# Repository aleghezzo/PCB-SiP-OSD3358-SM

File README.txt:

# 4 Layer PCB Based on SiP OSD3358-SM.
## Power Source - SMPS de 12/24V a 5V.
## LDO 3.3V.
## 2 USB Connectors: Host A y Device Micro B.
## MicroSD

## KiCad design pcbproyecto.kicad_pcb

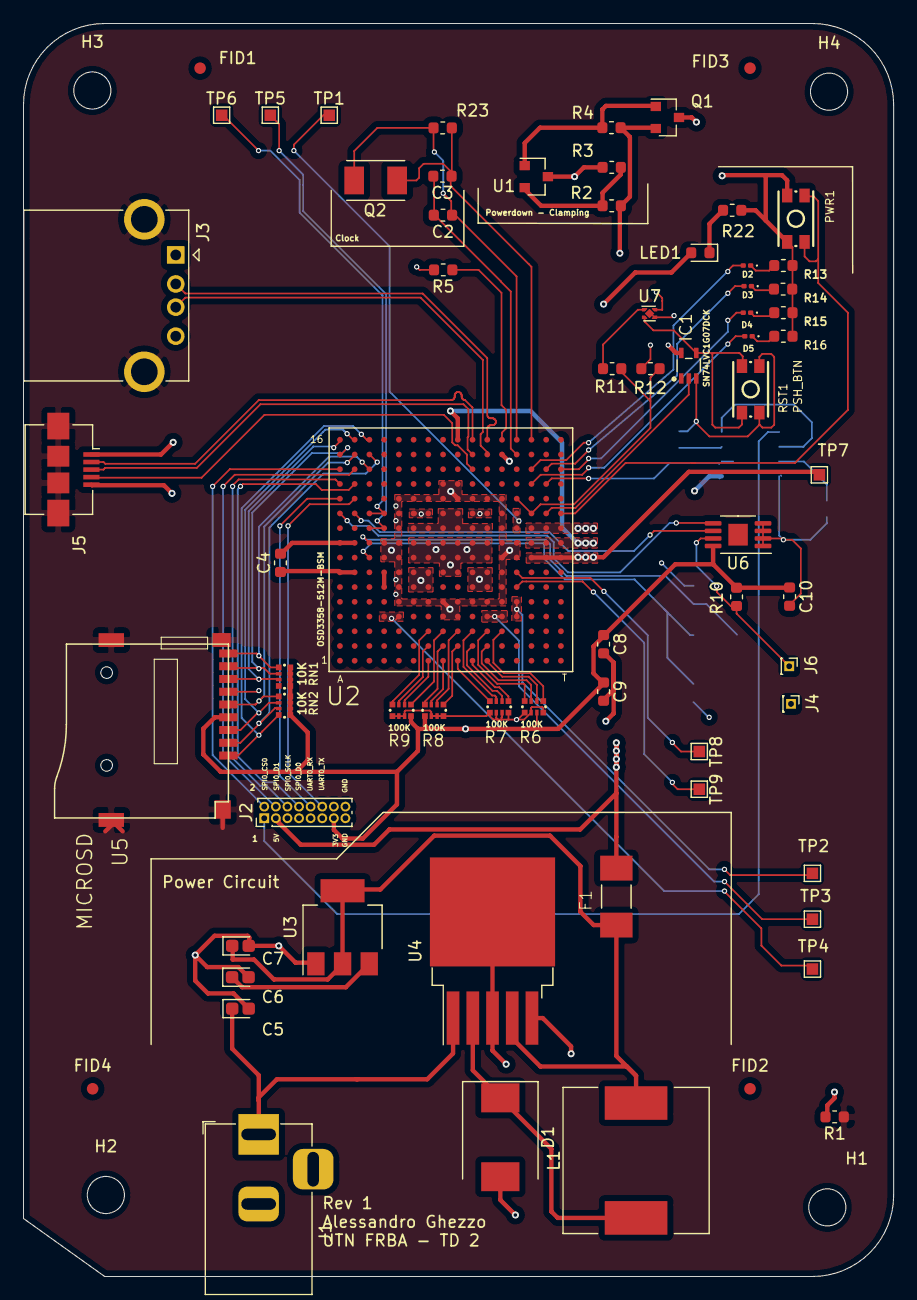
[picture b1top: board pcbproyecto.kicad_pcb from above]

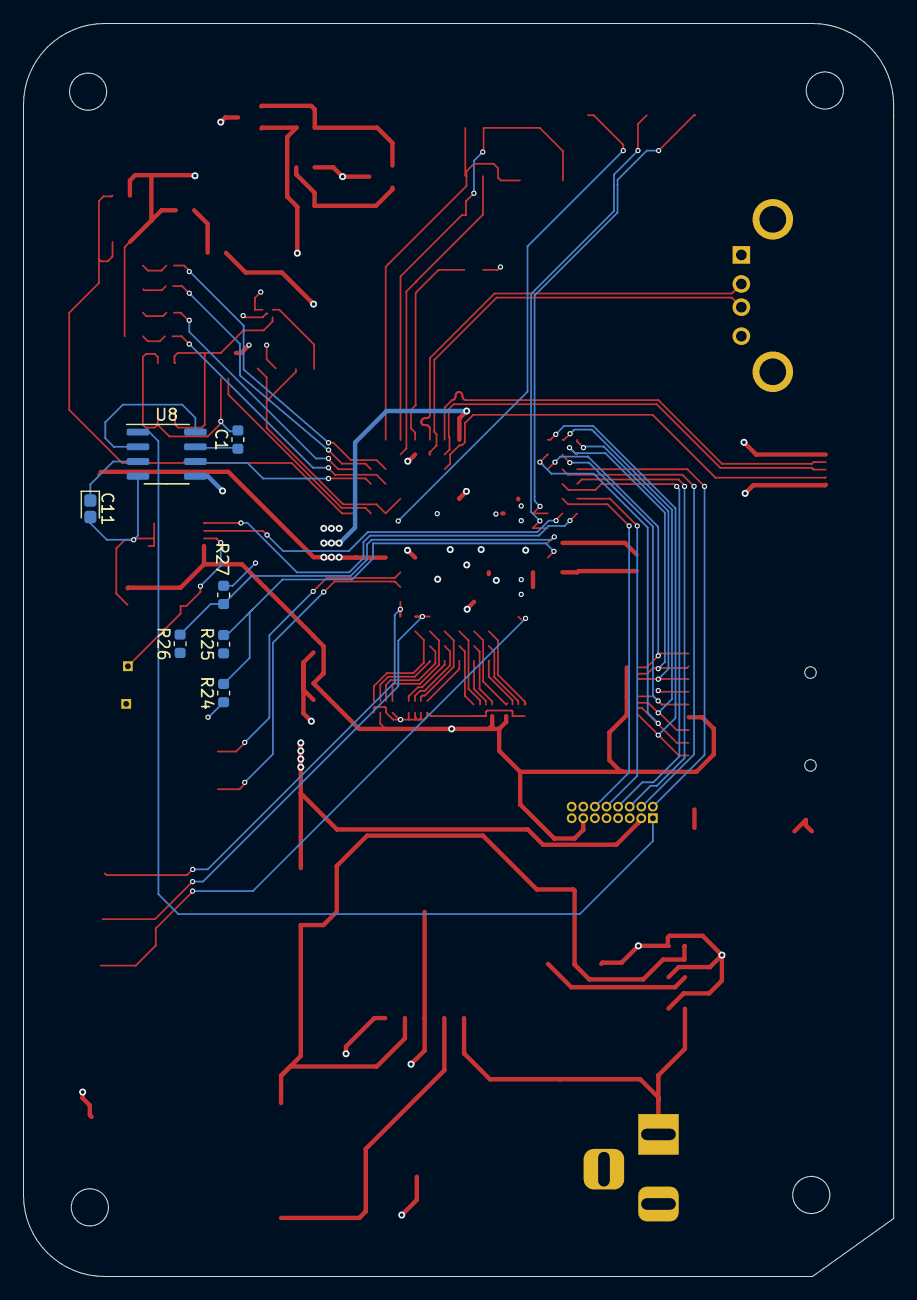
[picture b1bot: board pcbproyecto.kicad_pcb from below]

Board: 4 copper layers, 75.0 x 108.0 mm, 79 parts (7 on the bottom side), 91 nets.

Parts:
C1: 22pF; C_0603_1608Metric
C2, C3: 18pF, 50V; C_0603_1608Metric
C4, C10: 0.1uF, 6.3V; C_0603_1608Metric
C5: 100uF; CP_EIA-1608-08_AVX-J
C6: 100u; CP_EIA-1608-08_AVX-J
C7: 1000u; CP_EIA-1608-08_AVX-J
C8: 10uF, 10V; C_0603_1608Metric
C9: 0.1uF 6,3V; C_0603_1608Metric
C11: 470nF; CP_EIA-1608-08_AVX-J
D1: D_Schottky; D_SMC
D2, D3, D4, D5: LED; LED_0201_0603Metric
F1: Fuse; FUSC6125X279N
FID1, FID2, FID3, FID4: Fiducial; Fiducial_1mm_Mask2mm
H1, H2, H3, H4: MGT; MountingHole_3.2mm_M3
IC1: SN74LVC1G07DCK; SC70(TI-DCK)
J1: Barrel_Jack_Switch; BarrelJack_Horizontal
J2: Peripheral Header; PinHeader_2x08_P1.00mm_Vertical
J3: USB_A; USB_A_CONNFLY_DS1095-WNR0
J4: EEPROM_GND; PinHeader_1x01_P1.00mm_Vertical
J5: USB_B_Micro; USB_Micro-B_Amphenol_10104110_Horizontal
J6: EEPROM_WP; PinHeader_1x01_P1.00mm_Vertical
L1: 100uH; L_12x12mm_H6mm
LED1: L_PWR; LED_0603_1608Metric
PWR1: PSH_BTN; MINI_PUSHBUTTON
Q1: MMBT3906; SOT-23
Q2: 24 MHz; Crystal_SMD_TXC_7A-2Pin_5x3.2mm
R1: 0.1 5%; R_0603_1608Metric
R2, R5, R10, R24, R25, R26, R27: 10K; R_0603_1608Metric
R3: 40K; R_0603_1608Metric
R4: 500; R_0603_1608Metric
R6, R7, R8, R9: 100K; RN0804
R11, R12: 100K; R_0603_1608Metric
R13, R14, R15, R16: 1.5K; R_0603_1608Metric
R22: 1K; R_0603_1608Metric
R23: 1M , 1%; R_0603_1608Metric
RN1, RN2: 10K; RN0804
RST1: PSH_BTN; MINI_PUSHBUTTON
TP1: TP_PWR_EN; TestPoint_Pad_1.0x1.0mm
TP2: TP_PWRONSTN; TestPoint_Pad_1.0x1.0mm
TP3: TP_WAKEUP; TestPoint_Pad_1.0x1.0mm
TP4: TP_EXTINTN; TestPoint_Pad_1.0x1.0mm
TP5: TP_I2C_SCL; TestPoint_Pad_1.0x1.0mm
TP6: TP_I2C_SDA; TestPoint_Pad_1.0x1.0mm
TP7: TP_VIN_BAT; TestPoint_Pad_1.0x1.0mm
TP8: TP_SENSE_BAT; TestPoint_Pad_1.0x1.0mm
TP9: TP_TS_BAT; TestPoint_Pad_1.0x1.0mm
U1: TLVH431; SOT-23
U2: OSD3358-512M-BSM; OSD335X-BGA-256
U3: LM117_TO3; SOT-223-3_TabPin2
U4: LM2576HVS-5; TO-263-5_TabPin3
U5: MICROSD
U6: 24LC32; MSOP-8-1EP_3x3mm_P0.65mm_EP1.68x1.88mm
U7: TPS3831; Texas_X2SON-4_1x1mm_P0.65mm
U8: PCF8883; SOIC-8_3.9x4.9mm_P1.27mm

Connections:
+3V3: C6.1, U3.3
+5V: C7.1, F1.1, L1.2, U3.2, U4.4
/GPIO_A4: U2.R13, U8.6
/GPIO_A5: D5.2, U2.P13
/GPIO_A6: D4.2, U2.T14
/GPIO_A7: D3.2, U2.R14
/GPIO_A8: D2.2, U2.P14
/I2C1_SCL: U2.B11, U6.6
/I2C1_SDA: U2.A11, U6.5
/Interfaces/IN_PWR_SUPPLY: C5.1, J1.1, U4.1
/Interfaces/MMC0_CD: RN2.5, U2.C14, U5.9
/Interfaces/MMC0_CLK: RN1.5, U2.B15, U5.5
/Interfaces/MMC0_CMD: RN1.6, U2.B16, U5.3
/Interfaces/MMC0_DAT0: RN2.7, U2.A16, U5.7
/Interfaces/MMC0_DAT1: RN2.6, U2.A15, U5.8
/Interfaces/MMC0_DAT2: RN1.8, U2.C16, U5.1
/Interfaces/MMC0_DAT3: RN1.7, U2.C15, U5.2
/Interfaces/PWR_ON: PWR1.3, PWR1.4, U2.T11
/PMIC_PGOOD: IC1.2, U2.R11
/Peripherals/SPI0_CS0: J2.2, U2.A14
/Peripherals/SPI0_D0: J2.8, U2.B13
/Peripherals/SPI0_D1: J2.4, U2.B14
/Peripherals/SPI0_SCLK: J2.6, U2.A13
/Peripherals/UART0_RX: J2.10, U2.A12
/Peripherals/UART0_TX: J2.12, U2.B12
/Sistem In Package/AIN51.8V: R24.2, R25.2, U2.C8
/Sistem In Package/AIN61.8V: R26.2, R27.2, U2.C9
/Sistem In Package/LCD_D0_G3: R9.8, U2.G3
/Sistem In Package/LCD_D1_G2: R9.7, U2.G2
/Sistem In Package/LCD_D2_G1: R9.6, U2.G1
/Sistem In Package/LCD_D3_H3: R9.5, U2.H3
/Sistem In Package/LCD_D4_H2: R8.8, U2.H2
/Sistem In Package/LCD_D5_H1: R8.7, U2.H1
/Sistem In Package/LCD_D6_J3: R8.6, U2.J3
/Sistem In Package/LCD_D7_J2: R8.5, U2.J2
/Sistem In Package/LCD_D8_J1: R7.8, U2.J1
/Sistem In Package/LCD_D9_K3: R7.7, U2.K3
/Sistem In Package/LCD_D10_K2: R7.6, U2.K2
/Sistem In Package/LCD_D11_K1: R7.5, U2.K1
/Sistem In Package/LCD_D12_L3: R6.8, U2.L3
/Sistem In Package/LCD_D13_L2: R6.7, U2.L2
/Sistem In Package/LCD_D14_L1: R6.6, U2.L1
/Sistem In Package/LCD_D15_M3: R6.5, U2.M3
/Sistem In Package/OSC_GND: C2.2, C3.2, U2.N15
/Sistem In Package/OSC_IN: C3.1, Q2.2, R23.1, U2.P16
/Sistem In Package/OSC_OUT: C2.1, Q2.1, R23.2, U2.N16
/Sistem In Package/VREF+: C4.1, U2.A7, U2.B7
/Sistem In Package/VREF-: C4.2, U2.A9, U2.B9
/USB0_D+: J5.3, U2.K15
/USB0_D-: J5.2, U2.K16
/USB0_ID: J5.4, U2.K14
/USB1_D+: J3.3, U2.L15
/USB1_D-: J3.2, U2.L16
/USB1_VBU: J3.1, U2.M15
/WARMRST: R11.1, R12.1, U2.N12, U2.P11
CGND: J3.5, J5.6, R1.1, U5.G1, U5.G2, U5.G3, U5.G4
GND: C1.2, C5.2, C6.2, C7.2, C8.2, C9.2, C10.2, C11.2, D1.2, IC1.3, J1.2, J1.3, J2.15, J2.16, J3.4, J4.1, J5.5, PWR1.1, PWR1.2, R1.2, R5.2, R6.1, R6.2, R6.4, R7.1, R7.2, R7.3, R7.4, R8.2, R8.3, R8.4, R9.1, R9.2, R9.3, R12.2, R13.2, R14.2, R15.2, R16.2, R22.2, R24.1, R27.1, RST1.1, RST1.2, U2.D8, U2.D9, U2.E5, U2.E6, U2.E7, U2.E8, U2.E9, U2.E10, U2.E11, U2.E12, U2.F5, U2.F12, U2.G5, U2.G12, U2.H4, U2.H5, U2.H12, U2.H13, U2.J4, U2.J5, U2.J12, U2.J13, U2.K5, U2.K12, U2.L5, U2.L12, U2.M5, U2.M6, U2.M7, U2.M8, U2.M9, U2.M10, U2.M11, U2.M12, U2.N8, U2.N9, U3.1, U4.3, U4.5, U5.6, U6.1, U6.2, U6.3, U6.4, U7.3, U7.5, U8.4
unnamed: C1.1, U8.7
unnamed: C11.1, U8.3
unnamed: D1.1, L1.1, U4.2
unnamed: D2.1, R13.1
unnamed: D3.1, R14.1
unnamed: D4.1, R15.1
unnamed: D5.1, R16.1
unnamed: IC1.4, RST1.3, RST1.4, U7.2
unnamed: J2.1, U8.1
unnamed: J6.1, R10.2, U6.7
unnamed: LED1.1, R22.1
unnamed: Q1.1, R4.1, U1.1
unnamed: R2.2, R3.2, U1.2
unnamed: R5.1, U2.M16
unnamed: R11.2, U7.1
unnamed: TP1.1, U2.N10, U2.N11
unnamed: TP2.1, U2.N4, U2.N5
unnamed: TP3.1, U2.L4, U2.M4
unnamed: TP4.1, U2.D4, U2.E4
unnamed: TP5.1, U2.C10, U2.D10
unnamed: TP6.1, U2.C11, U2.D11
unnamed: TP7.1, U2.P8, U2.R8, U2.T8
unnamed: TP8.1, U2.N7
unnamed: TP9.1, U2.N6
unnamed: U2.D6, U2.D7
unnamed: U8.2, U8.8
SYS_5V: U2.K6, U2.K7, U2.L6, U2.L7
USB_DC: J5.1, U2.J16, U2.P9, U2.R9, U2.T9
VDD_1V8: U2.F10, U2.G10, U2.H10, U2.H11, U2.J10, U2.J11, U2.K10, U2.L10
VDD_3V3A: U2.F8, U2.F9, U2.G8, U2.G9, U2.H7, U2.H8, U2.H9, U2.J7, U2.J8, U2.J9, U2.K8, U2.K9, U2.L8, U2.L9
VDD_3V3AUX: LED1.2, U2.F11, U2.G11
VDD_3V3B: C8.1, C9.1, C10.1, J2.13, Q1.2, R2.1, R4.2, R6.3, R8.1, R9.4, R10.1, RN1.1, RN1.2, RN1.3, RN1.4, RN2.1, RN2.2, RN2.3, RN2.4, U2.F6, U2.F7, U2.G6, U2.G7, U5.4, U6.8, U7.4, U8.5
VDD_5V: F1.2, J2.3, U2.P10, U2.R10, U2.T10
VDD_RTC: IC1.5, Q1.3, R3.1, U1.3, U2.K11, U2.L11

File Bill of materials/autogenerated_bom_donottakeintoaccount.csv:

"Id";"Designator";"Package";"Quantity";"Designation";"Supplier and ref";
1;"F1";"FUSC6125X279N";1;"Fuse";;;
2;"C10,C4";"C_0603_1608Metric";2;"0.1uF, 6.3V";;;
3;"C9";"C_0603_1608Metric";1;"0.1uF 6,3V";;;
4;"C8";"C_0603_1608Metric";1;"10uF, 10V";;;
5;"C3,C2";"C_0603_1608Metric";2;"18pF, 50V";;;
6;"C1";"C_0603_1608Metric";1;"22pF";;;
7;"J3";"USB_A_CONNFLY_DS1095-WNR0";1;"USB_A";;;
8;"U8";"SOIC-8_3.9x4.9mm_P1.27mm";1;"PCF8883";;;
9;"C11";"CP_EIA-1608-08_AVX-J";1;"470nF";;;
10;"TP9";"TestPoint_Pad_1.0x1.0mm";1;"TP_TS_BAT";;;
11;"TP8";"TestPoint_Pad_1.0x1.0mm";1;"TP_SENSE_BAT";;;
12;"RST1,PWR1";"MINI_PUSHBUTTON";2;"PSH_BTN";;;
13;"R16,R15,R14,R13";"R_0603_1608Metric";4;"1.5K";;;
14;"D5,D4,D3,D2";"LED_0201_0603Metric";4;"LED";;;
15;"U7";"Texas_X2SON-4_1x1mm_P0.65mm";1;"TPS3831";;;
16;"R12,R11";"R_0603_1608Metric";2;"100K";;;
17;"IC1";"SC70(TI-DCK)";1;"SN74LVC1G07DCK";;;
18;"U6";"MSOP-8-1EP_3x3mm_P0.65mm_EP1.68x1.88mm";1;"24LC32";;;
19;"TP7";"TestPoint_Pad_1.0x1.0mm";1;"TP_VIN_BAT";;;
20;"TP6";"TestPoint_Pad_1.0x1.0mm";1;"TP_I2C_SDA";;;
21;"TP5";"TestPoint_Pad_1.0x1.0mm";1;"TP_I2C_SCL";;;
22;"TP4";"TestPoint_Pad_1.0x1.0mm";1;"TP_EXTINTN";;;
23;"TP3";"TestPoint_Pad_1.0x1.0mm";1;"TP_WAKEUP";;;
24;"TP2";"TestPoint_Pad_1.0x1.0mm";1;"TP_PWRONSTN";;;
25;"TP1";"TestPoint_Pad_1.0x1.0mm";1;"TP_PWR_EN";;;
26;"J2";"PinHeader_2x08_P1.00mm_Vertical";1;"Peripheral Header";;;
27;"R27,R26,R25,R24,R10,R5,R2";"R_0603_1608Metric";7;"10K";;;
28;"J6";"PinHeader_1x01_P1.00mm_Vertical";1;"EEPROM_WP";;;
29;"J4";"PinHeader_1x01_P1.00mm_Vertical";1;"EEPROM_GND";;;
30;"FID4,FID3,FID2,FID1";"Fiducial_1mm_Mask2mm";4;"Fiducial";;;
31;"U5";"MICROSD";1;"MICROSD";;;
32;"RN2,RN1";"RN0804";2;"10K";;;
33;"J5";"USB_Micro-B_Amphenol_10104110_Horizontal";1;"USB_B_Micro";;;
34;"C5";"CP_EIA-1608-08_AVX-J";1;"100uF";;;
35;"C6";"CP_EIA-1608-08_AVX-J";1;"100u";;;
36;"C7";"CP_EIA-1608-08_AVX-J";1;"1000u";;;
37;"J1";"BarrelJack_Horizontal";1;"Barrel_Jack_Switch";;;
38;"R9,R8,R7,R6";"RN0804";4;"100K";;;
39;"U4";"TO-263-5_TabPin3";1;"LM2576HVS-5";;;
40;"U3";"SOT-223-3_TabPin2";1;"LM117_TO3";;;
41;"U2";"OSD335X-BGA-256";1;"OSD3358-512M-BSM";;;
42;"U1";"SOT-23";1;"TLVH431";;;
43;"R23";"R_0603_1608Metric";1;"1M , 1%";;;
44;"Q2";"Crystal_SMD_TXC_7A-2Pin_5x3.2mm";1;"24 MHz";;;
45;"R3";"R_0603_1608Metric";1;"40K";;;
46;"R4";"R_0603_1608Metric";1;"500";;;
47;"Q1";"SOT-23";1;"MMBT3906";;;
48;"R1";"R_0603_1608Metric";1;"0.1 5%";;;
49;"H4,H3,H2,H1";"MountingHole_3.2mm_M3";4;"MGT";;;
50;"R22";"R_0603_1608Metric";1;"1K";;;
51;"LED1";"LED_0603_1608Metric";1;"L_PWR";;;
52;"D1";"D_SMC";1;"D_Schottky";;;
53;"L1";"L_12x12mm_H6mm";1;"100uH";;;

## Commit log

2020-07-30 Progress
2020-07-31 EMD Protection
2020-08-03 Progress - No custom peripheral
2020-08-04 README
2020-08-05 WIP - Docs & Gerbers (no custom peripheric yet)
2020-08-06 Custom Peripheral, Gerbers, drills
2020-08-06 Bill of Materials + Some 3D Models
2020-08-09 Checklist & Small changes, new docs & gerbers
2020-08-16 DRC Fixes and more
